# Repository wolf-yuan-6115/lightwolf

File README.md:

# LightWolf

> Sponsored by [Hack Club Blueprint](https://blueprint.hackclub.com/r/137?ref=r) program
> 
> To meet program requirements, `JOURNAL.md` and `bom.csv` files are included in this repository root.

LightWolf is a recreate version of Raspberry Pi Pico development board created by me. It's used to experiment with PCB designing and electronics.

Currently, LightWolf comes with following vairants:
- **LightWolf 2350** (`/2350`): Raspberry Pi RP2350 based development board with 4 MB of flash, USB C connector, a bunch of GPIO pins and 3 user LEDs.

> Depending on my free time, I may create more variants of LightWolf in the future.

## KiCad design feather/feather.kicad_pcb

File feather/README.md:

# Feather

A USB DAC that provides even better audio quality compared to Pumper. Since I want to make the board as small as possible, the board itself is only 6x4 cm.

This board has two outputs: One is 3.5mm unbalanced output, another one is 4.4mm balanced, for headphone that supports this and it can provide more power through this port.

## Why Feather?

Due to being *half* Hi-Fi fan, I want to try out some new method to get better audio. Like previous project Pumper, already got amazing power to drive headphone. Though it has some flaw and I think it's got not very balanced sound profile.

Feather is aimed to elimate the problem encountered on Pumper, with improved DAC and op-amp and one more balanced output. It should be a lot better at driving headphone and provide good audio.

## Images

> It's a 4 layer board, with dedicated GND plane and power plane.

## BOM

| Name         | Cost        |
| ------------ | ----------- |
| PCB Shipping | $4.86       |
| PCB Assambly | $117.63     |
| PCB          | $7.00       |
| Coupon       | $-9.00      |
| **Total**    | **$120.49** |

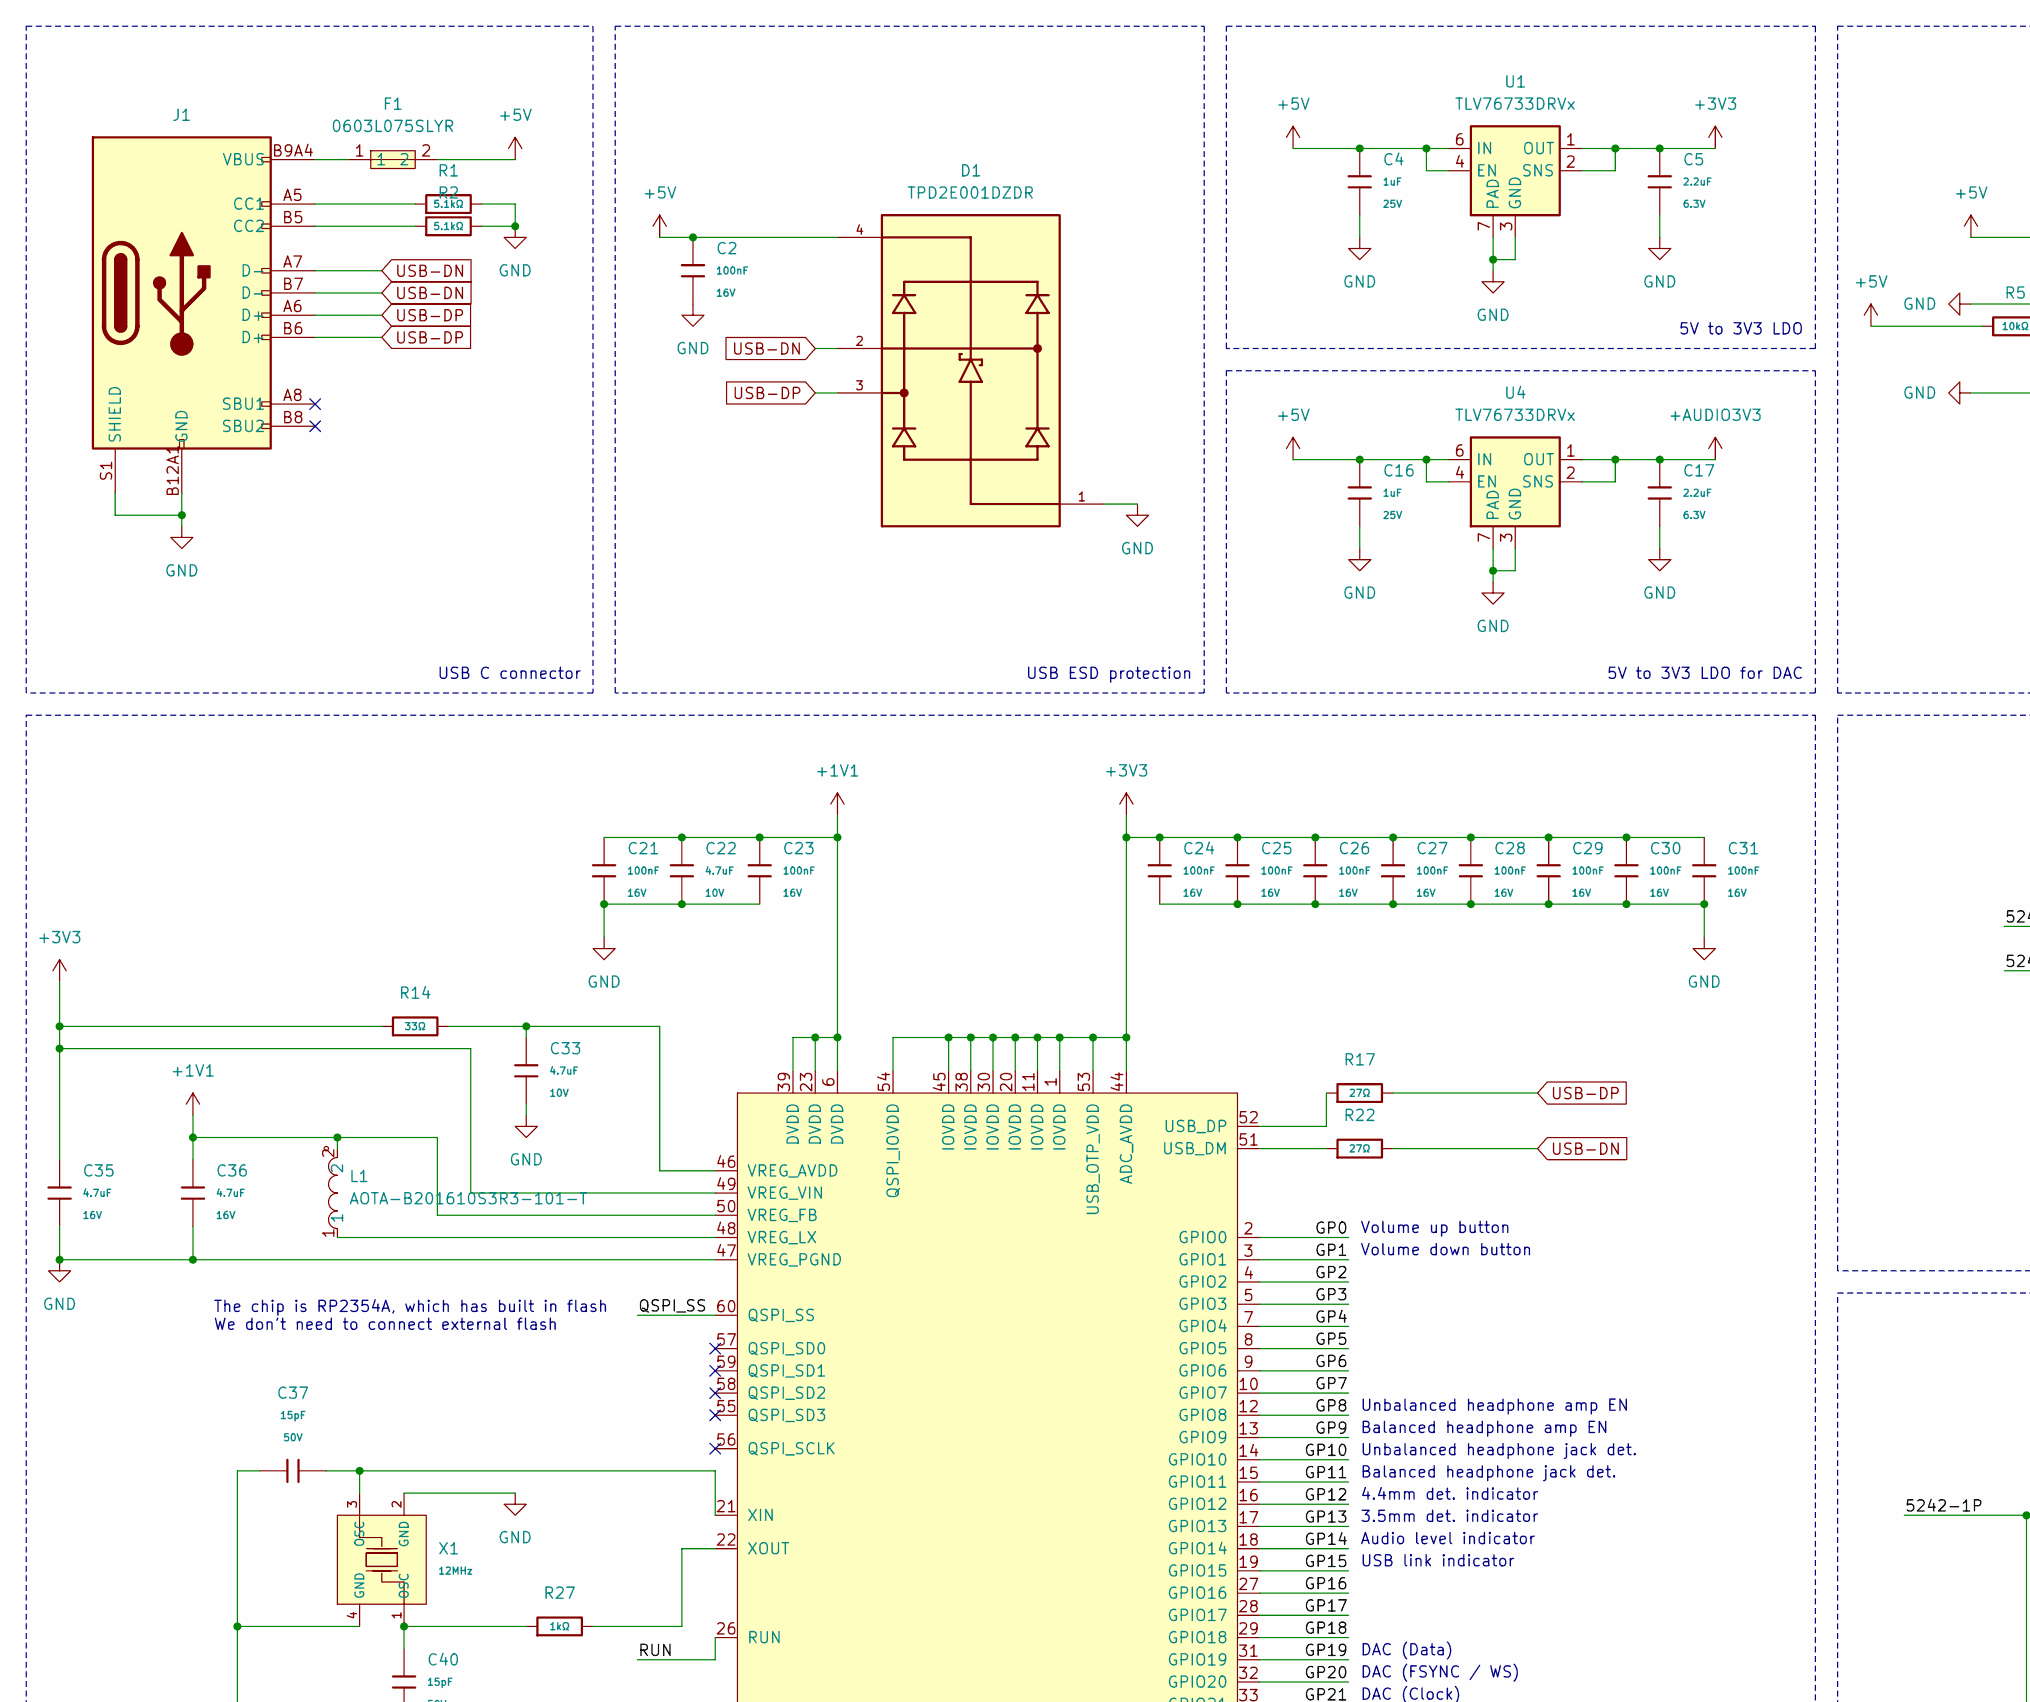
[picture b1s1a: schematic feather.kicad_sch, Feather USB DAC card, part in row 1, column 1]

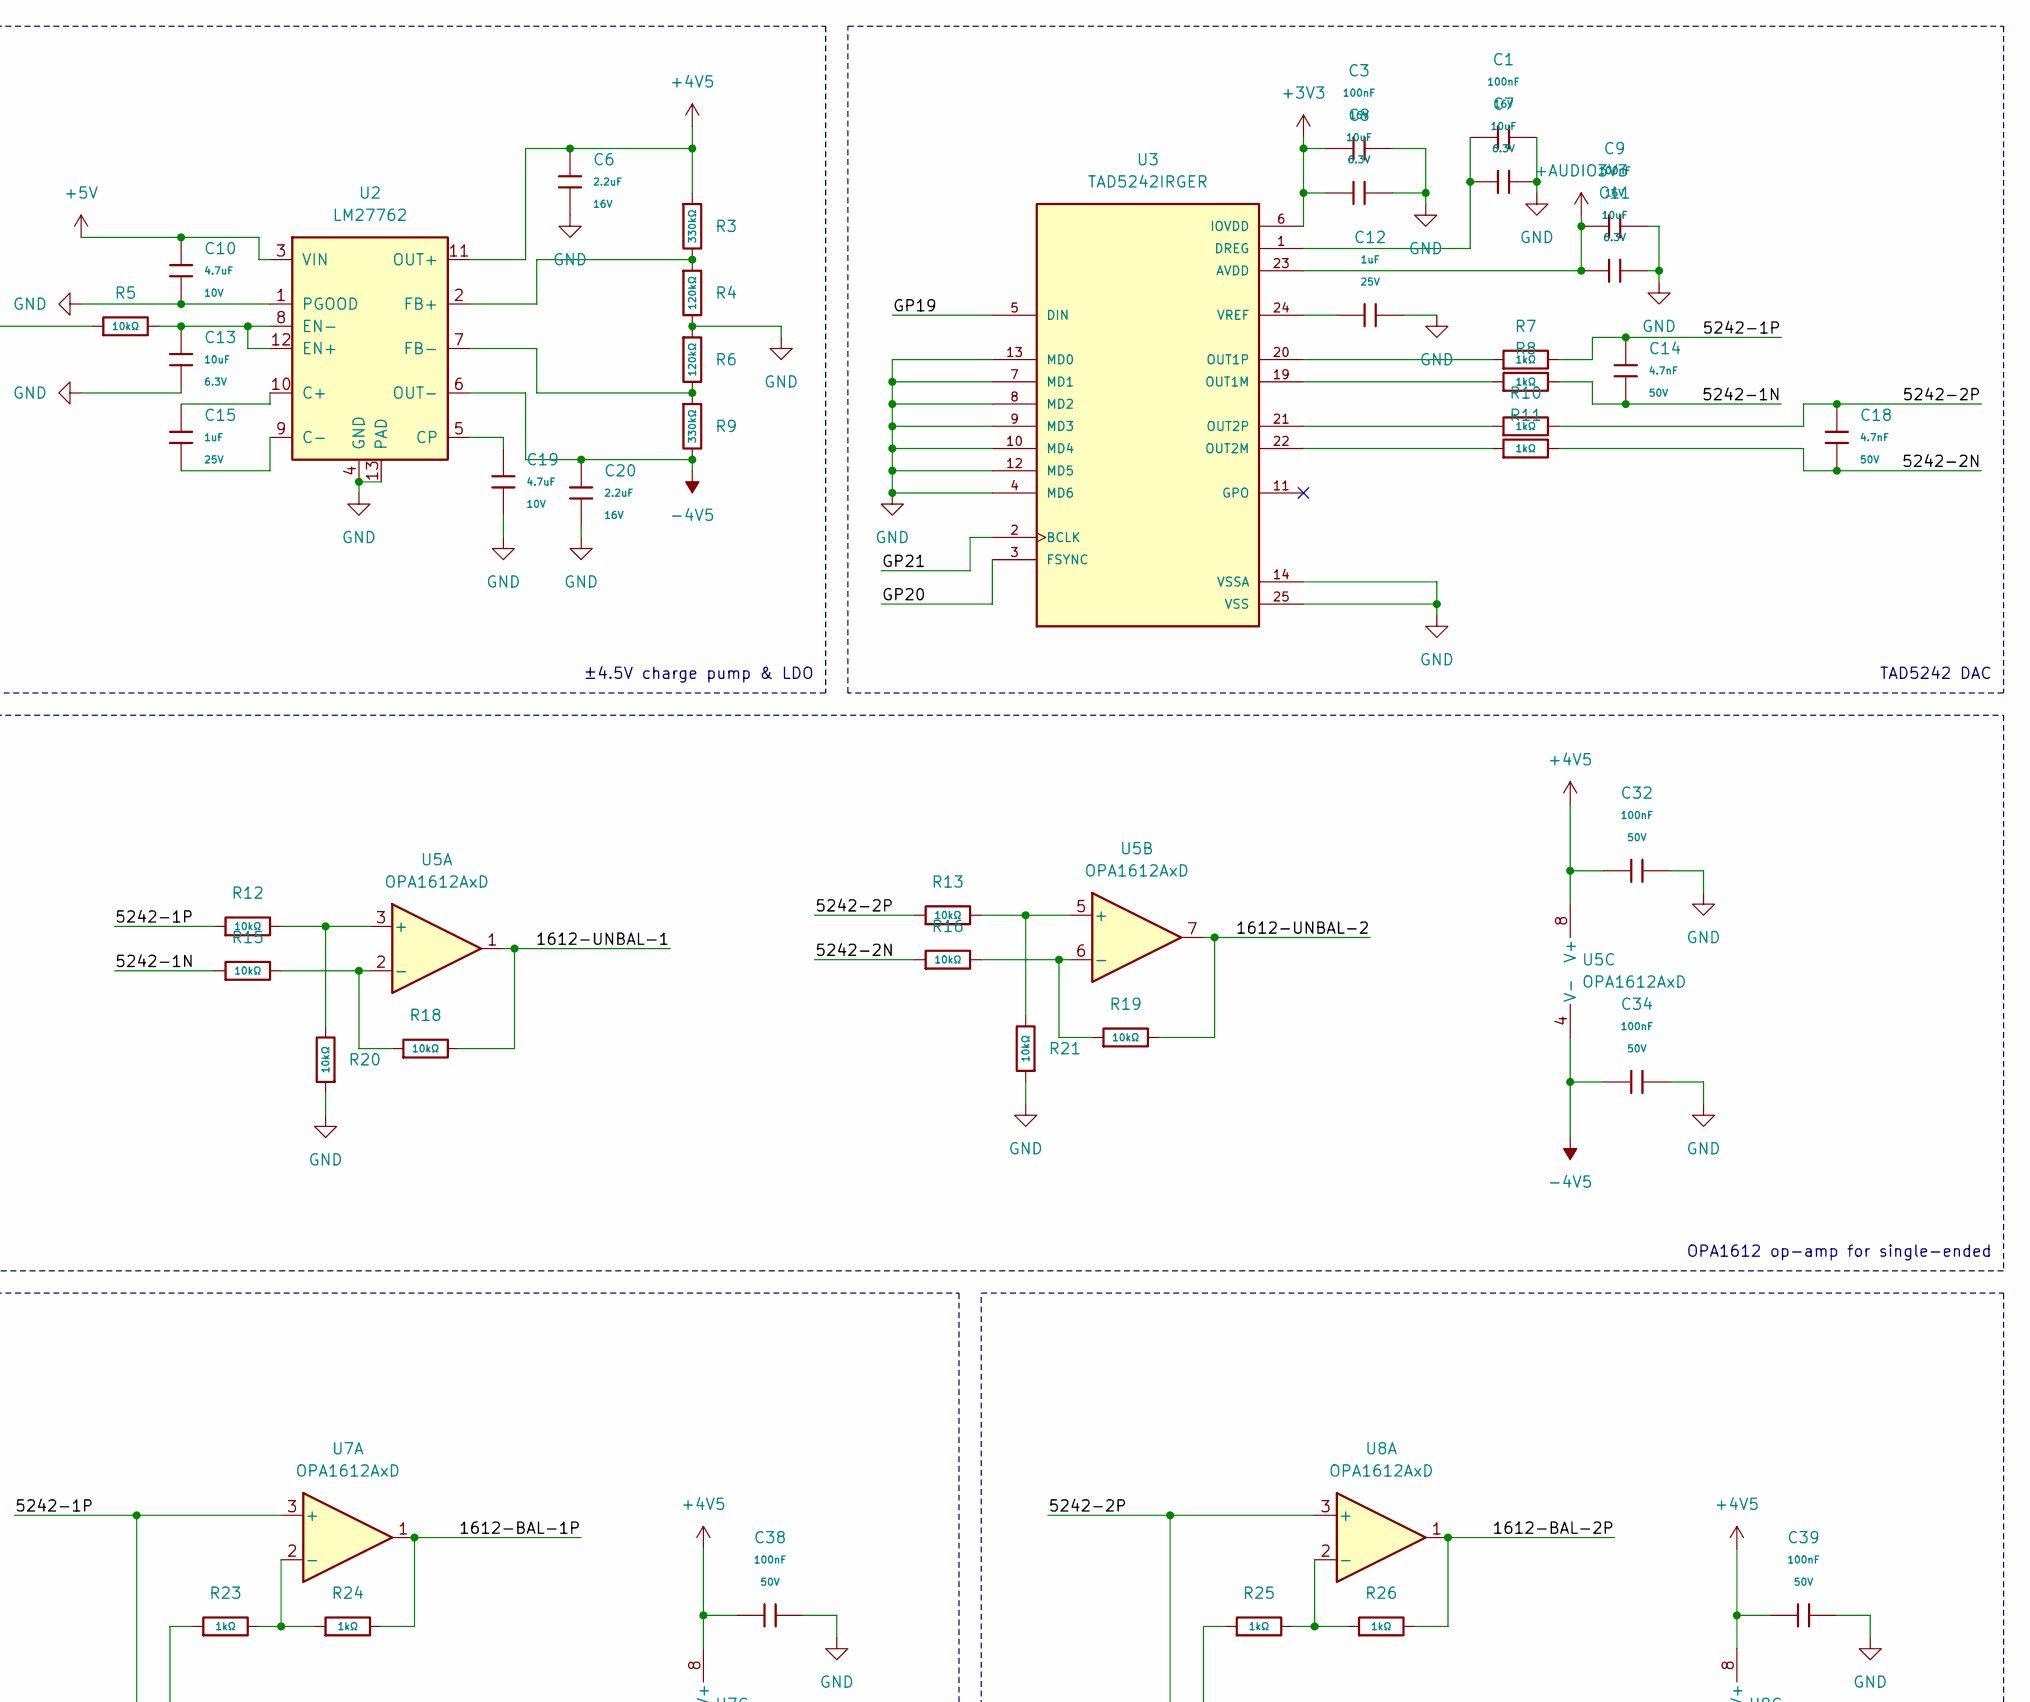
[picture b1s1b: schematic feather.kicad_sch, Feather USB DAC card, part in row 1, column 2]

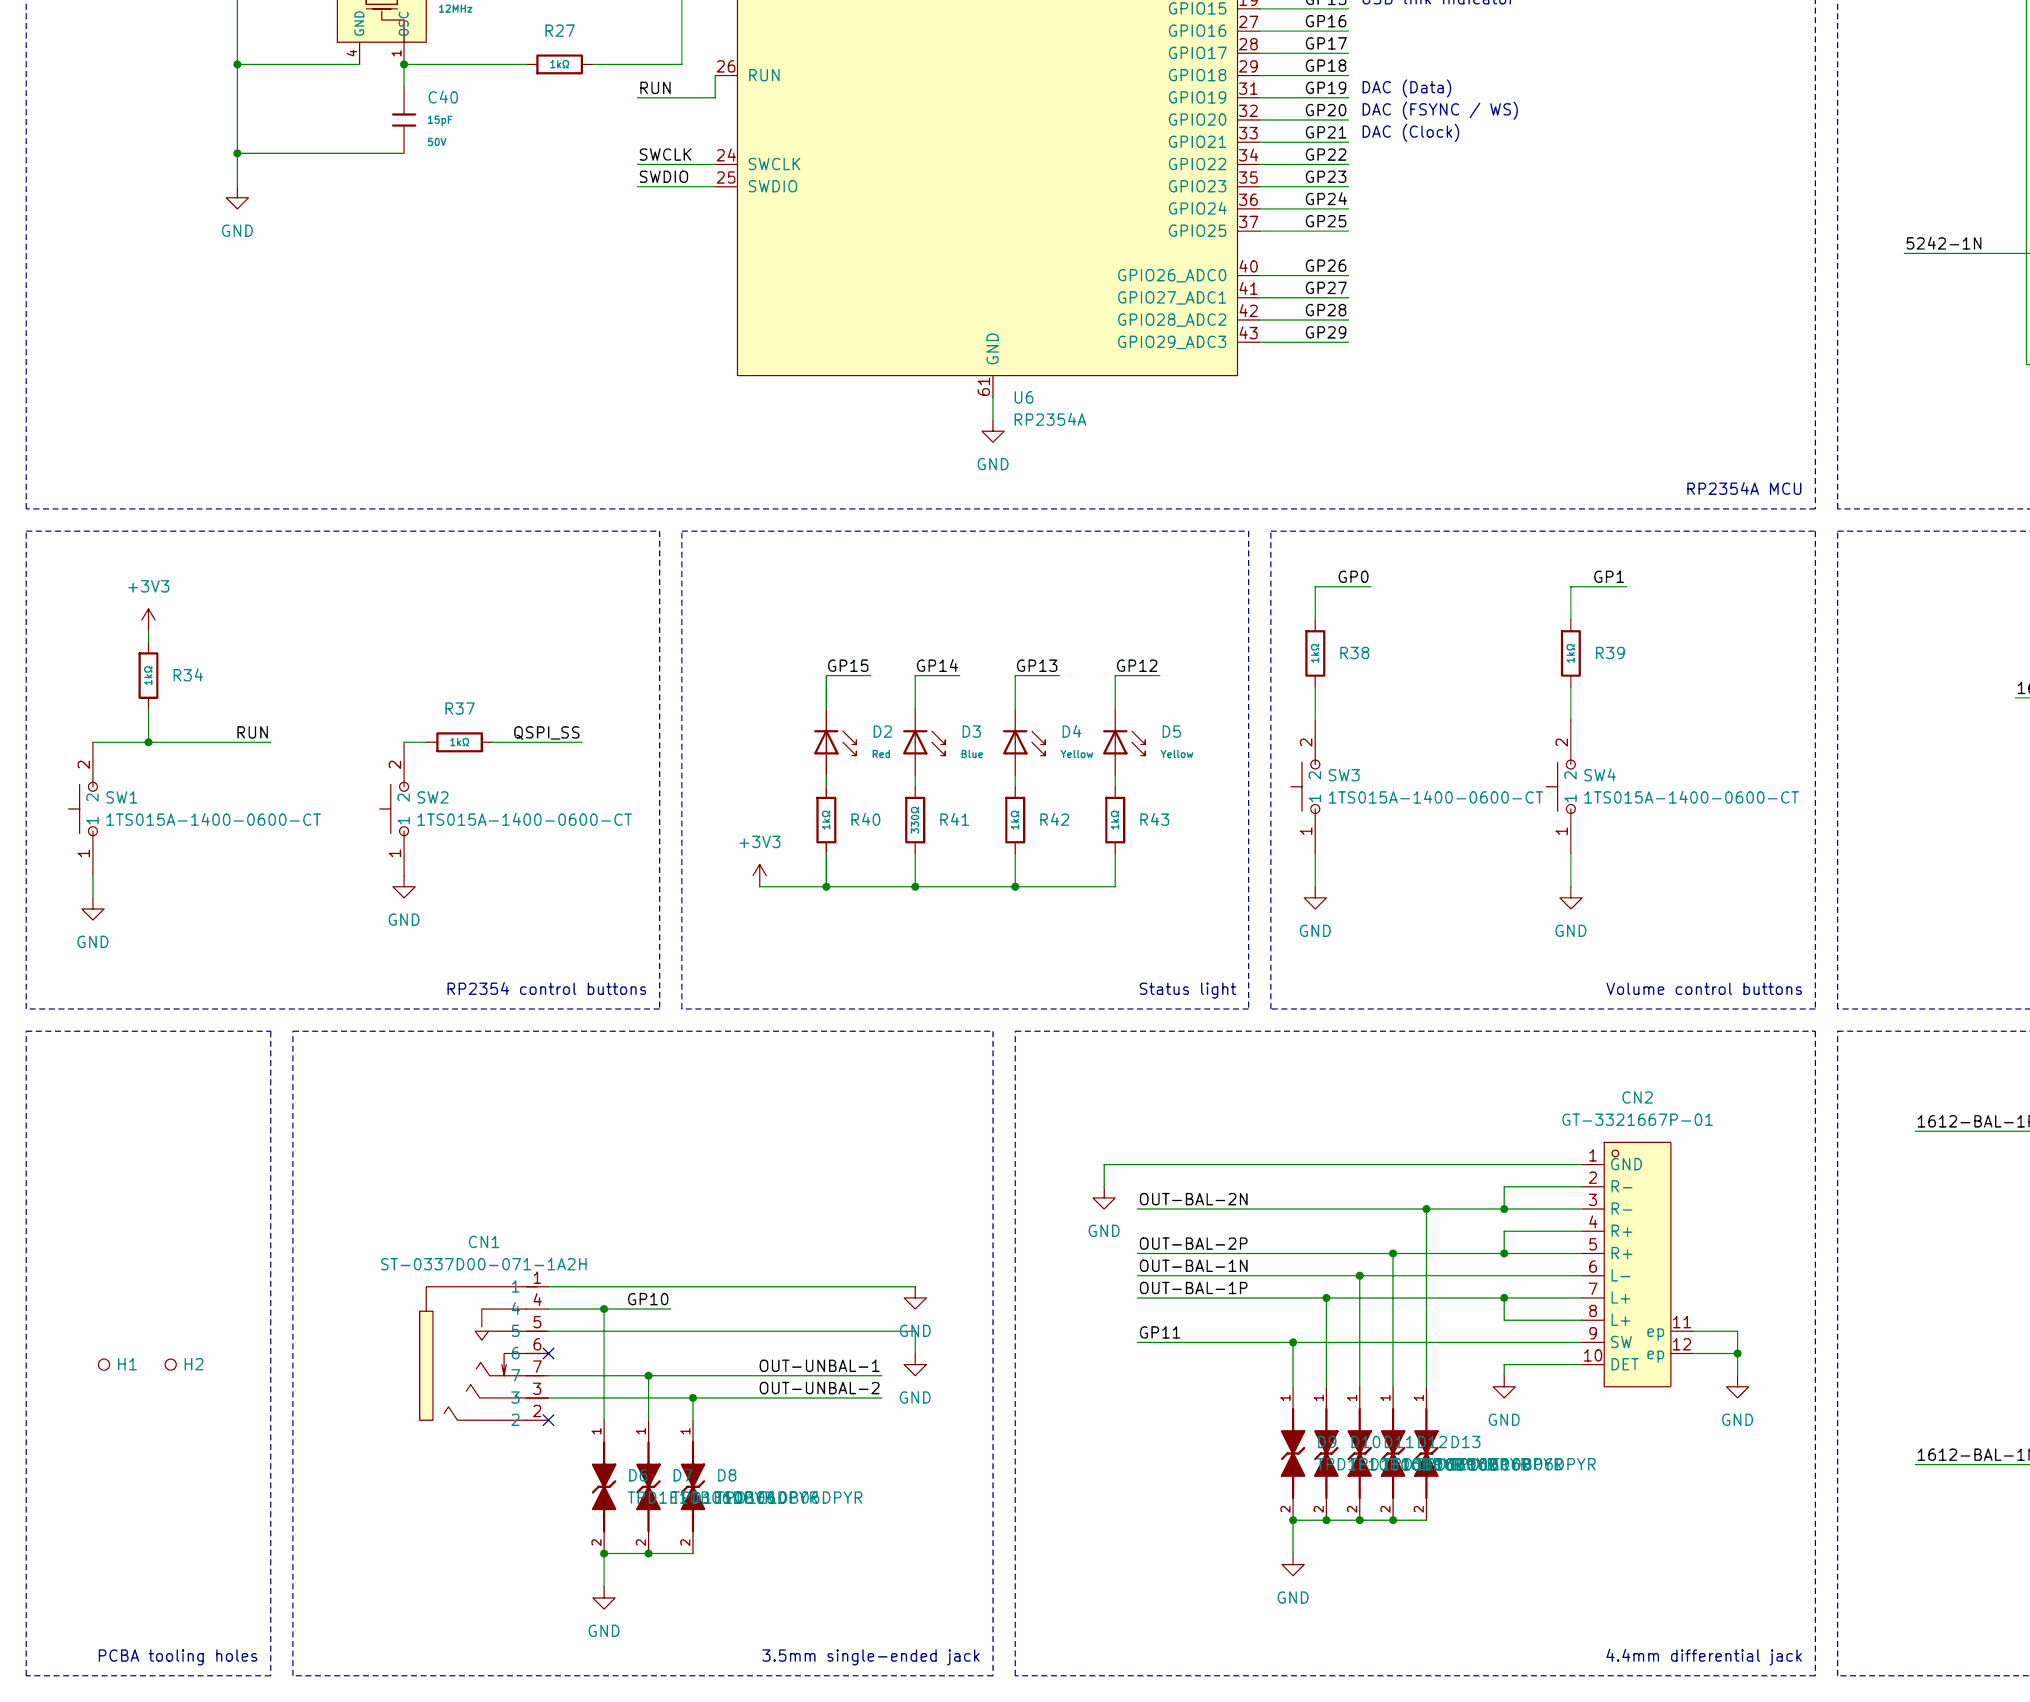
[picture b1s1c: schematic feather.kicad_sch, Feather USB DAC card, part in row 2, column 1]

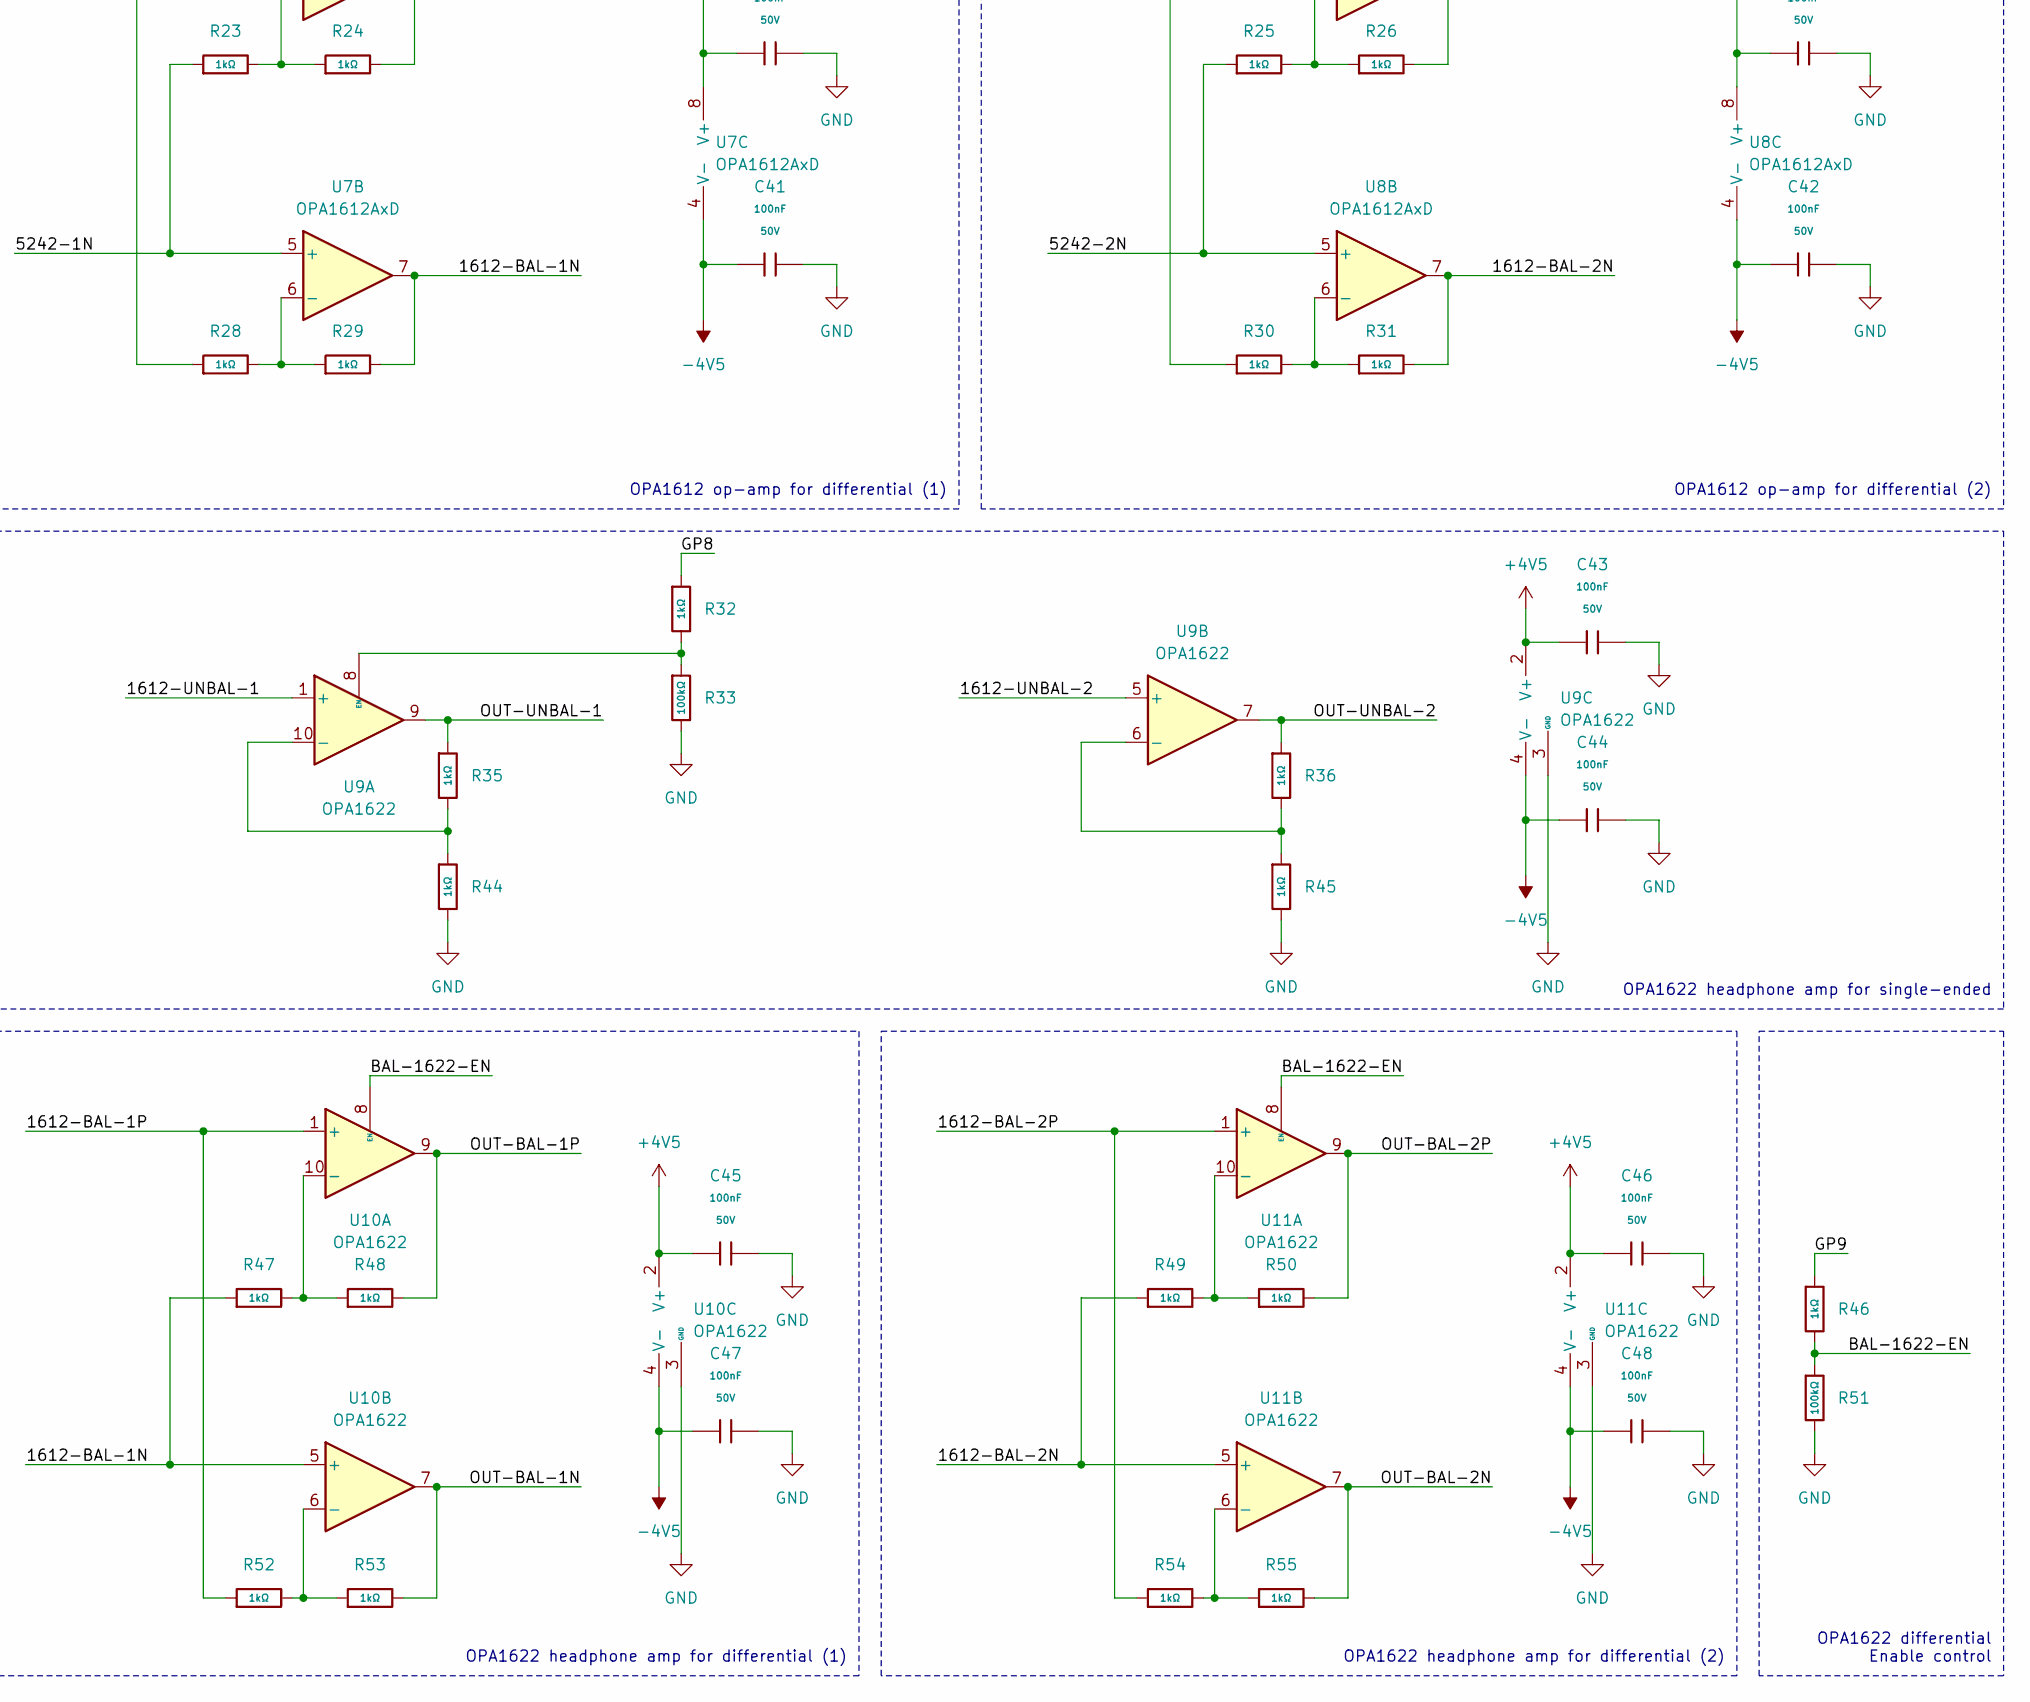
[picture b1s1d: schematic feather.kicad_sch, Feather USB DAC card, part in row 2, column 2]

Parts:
C1, C2, C3, C9, C21, C23, C24, C25, C26, C27, C28, C29, C30, C31: 100nF; C_0402; Voltage Rated 16V; Tolerance ±10%; Part CL05B104KO5NNNC; LCSC C1525
C4, C12, C15, C16: 1uF; C_0402; Voltage Rated 25V; Tolerance ±10%; Part CL05A105KA5NQNC; LCSC C52923
C5, C17: 2.2uF; C_0402; Voltage Rated 6.3V; Tolerance ±20%; Part CL05A225MQ5NSNC; LCSC C12530
C6, C20: 2.2uF; C_0603; Voltage Rated 16V; Tolerance ±10%; Part CL10A225KO8NNNC; LCSC C23630
C7, C8, C11, C13: 10uF; C_0402; Voltage Rated 6.3V; Tolerance ±20%; Part CL05A106MQ5NUNC; LCSC C15525
C10, C19, C22, C33: 4.7uF; C_0402; Voltage Rated 10V; Tolerance ±20%; Part CL05A475MP5NRNC; LCSC C23733
C14, C18: 4.7nF; C_0402; Voltage Rated 50V; Tolerance ±10%; Part 0402B472K500NT; LCSC C1538
C32: 100nF; C_0402; Voltage Rated 50V; Tolerance ±10%; Part CL05B104KB54PNC; LCSC C1525
C34, C38, C39, C41, C42, C43, C44, C45, C46, C47, C48: 100nF; C_0402; Voltage Rated 50V; Tolerance ±10%; Part CL05B104KB54PNC; LCSC C307331
C35, C36: 4.7uF; C_0603; Voltage Rated 16V; Tolerance ±10%; Part CL10A475KO8NNNC; LCSC C19666
C37, C40: 15pF; C_0402; Voltage Rated 50V; Tolerance ±5%; Part 0402CG150J500NT; LCSC C1548
CN1: ST-0337D00-071-1A2H; AUDIO-TH_ST-0337D00-071-1A2H; MPN ST-0337D00-071-1A2H; LCSC Part C2829972
CN2: GT-3321667P-01; AUDIO-TH_GT-3321667P-01; MPN GT-3321667P-01; LCSC Part C2762984
D1: TPD2E001DZDR; SOT192P237X122-4N; PARTREV I; LCSC C89411
D2: Red; D_0603; Forward Voltage (VF) 1.6V~2.6V; Part KT-0603R; LCSC C2286
D3: Blue; D_0603; LCSC C7496823
D4, D5: Yellow; D_0603; Forward Voltage (VF) 1.6V~2.6V; Part NCD0603Y2; LCSC C89811
D6, D7, D8, D9, D10, D11, D12, D13: TPD1E10B06DPYR; DIO_TPD1E10B06DPYR; PARTREV G; LCSC C48260
F1: 0603L075SLYR; Fuse_0603_1608Metric; LCSC Part C207016
H1, H2: Hole_Tooling_JLCPCB
J1: Connector, USB-TYPE-C-16P; TYPE-C-SMD_HX-TYPE-C-16PIN; LCSC C2927039
L1: AOTA-B201610S3R3-101-T; IND-SMD_L2.0-W1.6_AOTA-B201610S3R3-101-T; LCSC Part C42411119
R1, R2: 5.1kΩ; R_0402; Overload Voltage (Max) 50V; Tolerance ±1%; Part 0402WGF5101TCE; LCSC C25905
R3, R9: 330kΩ; R_0603; Overload Voltage (Max) 75V; Tolerance ±1%; Part 0603WAF3303T5E; LCSC C23137
R4, R6: 120kΩ; R_0603; Overload Voltage (Max) 75V; Tolerance ±1%; Part 0603WAF1203T5E; LCSC C25808
R5, R18, R19, R20, R21: 10kΩ; R_0402; Overload Voltage (Max) 50V; Tolerance ±1%; Part 0402WGF1002TCE; LCSC C25744
R7, R8, R10, R11, R23, R24, R25, R26, R27, R28, R29, R30, R31, R32, R34, R35, R36, R37, R38, R39, R40, R42, R43, R44, R45, R46, R47, R48, R49, R50, R52, R53, R54, R55: 1kΩ; R_0402; Overload Voltage (Max) 50V; Tolerance ±1%; Part 0402WGF1001TCE; LCSC C11702
R12, R13, R15, R16: 10kΩ; R_0603; Overload Voltage (Max) 75V; Tolerance ±1%; Part 0603WAF1002T5E; LCSC C25804
R14: 33Ω; R_0402; Overload Voltage (Max) 50V; Tolerance ±1%; Part 0402WGF330JTCE; LCSC C25105
R17, R22: 27Ω; R_0603; Overload Voltage (Max) 75V; Tolerance ±1%; Part 0603WAF270JT5E; LCSC C25190
R33, R51: 100kΩ; R_0402; Overload Voltage (Max) 50V; Tolerance ±1%; Part 0402WGF1003TCE; LCSC C25741
R41: 330Ω; R_0402; Overload Voltage (Max) 50V; Tolerance ±1%; Part 0402WGF3300TCE; LCSC C25104
SW1, SW2, SW3, SW4: 1TS015A-1400-0600-CT; SW-SMD_L3.0-W2.0-LS3.5; LCSC Part C319433
U1, U4: TLV76733DRVx; WSON-6-1EP_2x2mm_P0.65mm_EP1x1.6mm_ThermalVias; LCSC C2848334
U2: LM27762; WSON-12-1EP_3x2mm_P0.5mm_EP1x2.65_ThermalVias; LCSC C473398
U3: TAD5242IRGER; IC_TAD5242IRGER; PARTREV A; LCSC C42414591
U5, U7, U8: OPA1612AxD; WSON-8-1EP_3x3mm_P0.5mm_EP1.2x2mm_ThermalVias; LCSC C2058640
U6: RP2354A; QFN-60-1EP_7x7mm_P0.4mm_EP3.4x3.4mm_ThermalVias; LCSC C42411118
U9, U10, U11: OPA1622; Texas_S-PVSON-N10_ThermalVias; LCSC C2876559
X1: 12MHz; OSC-SMD_4P-L3.2-W2.5-BL_SIT8008BI; LCSC C20625731

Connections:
+1V1: C21.1, C22.1, C23.1, C36.1, L1.2, U6.6 (DVDD), U6.23 (DVDD), U6.39 (DVDD), U6.50 (VREG_FB)
+3V3: C3.1, C5.1, C8.1, C24.1, C25.1, C26.1, C27.1, C28.1, C29.1, C30.1, C31.1, C35.1, R14.1, R34.1, R40.2, R41.2, R42.2, R43.2, U1.1 (OUT), U1.2 (SNS), U3.6 (IOVDD), U6.1 (IOVDD), U6.11 (IOVDD), U6.20 (IOVDD), U6.30 (IOVDD), U6.38 (IOVDD), U6.44 (ADC_AVDD), U6.45 (IOVDD), U6.49 (VREG_VIN), U6.53 (USB_OTP_VDD), U6.54 (QSPI_IOVDD)
+4V5: C6.1, C32.1, C38.1, C39.1, C43.1, C45.1, C46.1, R3.1, U2.11 (OUT+), U5.8 (V+), U7.8 (V+), U8.8 (V+), U9.2 (V+), U10.2 (V+), U11.2 (V+)
+5V: C2.1, C4.1, C10.1, C16.1, D1.4, F1.2, R5.1, U1.4 (EN), U1.6 (IN), U2.3 (VIN), U4.4 (EN), U4.6 (IN)
+AUDIO3V3: C9.1, C11.1, C17.1, U3.23 (AVDD), U4.1 (OUT), U4.2 (SNS)
-4V5: C20.1, C34.1, C41.1, C42.1, C44.1, C47.1, C48.1, R9.2, U2.6 (OUT-), U5.4 (V-), U7.4 (V-), U8.4 (V-), U9.4 (V-), U9.11 (V-), U10.4 (V-), U10.11 (V-), U11.4 (V-), U11.11 (V-)
/1612-BAL-1N: R29.2, R47.1, U7.7, U10.5 (+)
/1612-BAL-1P: R24.2, R52.1, U7.1, U10.1 (+)
/1612-BAL-2N: R31.2, R49.1, U8.7, U11.5 (+)
/1612-BAL-2P: R26.2, R54.1, U8.1, U11.1 (+)
/1612-UNBAL-1: R18.2, U5.1, U9.1 (+)
/1612-UNBAL-2: R19.2, U5.7, U9.5 (+)
/5242-1N: C14.2, R8.2, R15.1, R23.1, U7.5 (+)
/5242-1P: C14.1, R7.2, R12.1, R28.1, U7.3 (+)
/5242-2N: C18.2, R11.2, R16.1, R25.1, U8.5 (+)
/5242-2P: C18.1, R10.2, R13.1, R30.1, U8.3 (+)
/BAL-1622-EN: R46.2, R51.1, U10.8 (EN), U11.8 (EN)
/GP0: R38.1, U6.2 (GPIO0)
/GP1: R39.1, U6.3 (GPIO1)
/GP2: U6.4 (GPIO2)
/GP3: U6.5 (GPIO3)
/GP4: U6.7 (GPIO4)
/GP5: U6.8 (GPIO5)
/GP6: U6.9 (GPIO6)
/GP7: U6.10 (GPIO7)
/GP8: R32.1, U6.12 (GPIO8)
/GP9: R46.1, U6.13 (GPIO9)
/GP10: CN1.4, D6.1, U6.14 (GPIO10)
/GP11: CN2.9 (SW), D9.1, U6.15 (GPIO11)
/GP12: D5.1, U6.16 (GPIO12)
/GP13: D4.1, U6.17 (GPIO13)
/GP14: D3.1, U6.18 (GPIO14)
/GP15: D2.1, U6.19 (GPIO15)
/GP16: U6.27 (GPIO16)
/GP17: U6.28 (GPIO17)
/GP18: U6.29 (GPIO18)
/GP19: U3.5 (DIN), U6.31 (GPIO19)
/GP20: U3.3 (FSYNC), U6.32 (GPIO20)
/GP21: U3.2 (BCLK), U6.33 (GPIO21)
/GP22: U6.34 (GPIO22)
/GP23: U6.35 (GPIO23)
/GP24: U6.36 (GPIO24)
/GP25: U6.37 (GPIO25)
/GP26: U6.40 (GPIO26_ADC0)
/GP27: U6.41 (GPIO27_ADC1)
/GP28: U6.42 (GPIO28_ADC2)
/GP29: U6.43 (GPIO29_ADC3)
/OUT-BAL-1N: CN2.6 (L-), D11.1, R53.2, U10.7
/OUT-BAL-1P: CN2.7 (L+), CN2.8 (L+), D10.1, R48.2, U10.9
/OUT-BAL-2N: CN2.2 (R-), CN2.3 (R-), D13.1, R55.2, U11.7
/OUT-BAL-2P: CN2.4 (R+), CN2.5 (R+), D12.1, R50.2, U11.9
/OUT-UNBAL-1: CN1.7, D7.1, R35.1, U9.9
/OUT-UNBAL-2: CN1.3, D8.1, R36.1, U9.7
/QSPI_SS: R37.2, U6.60 (QSPI_SS)
/RUN: R34.2, SW1.2, U6.26 (RUN)
/SWCLK: U6.24 (SWCLK)
/SWDIO: U6.25 (SWDIO)
GND: C1.2, C2.2, C3.2, C4.2, C5.2, C6.2, C7.2, C8.2, C9.2, C10.2, C11.2, C12.2, C13.2, C16.2, C17.2, C19.2, C20.2, C21.2, C22.2, C23.2, C24.2, C25.2, C26.2, C27.2, C28.2, C29.2, C30.2, C31.2, C32.2, C33.2, C34.2, C35.2, C36.2, C37.1, C38.2, C39.2, C40.2, C41.2, C42.2, C43.2, C44.2, C45.2, C46.2, C47.2, C48.2, CN1.1, CN1.5, CN2.1 (GND), CN2.10 (DET), CN2.11 (ep), CN2.12 (ep), D1.1, D6.2, D7.2, D8.2, D9.2, D10.2, D11.2, D12.2, D13.2, J1.A12B1 (GND), J1.B12A1 (GND), J1.S1 (SHIELD), R1.2, R2.2, R4.2, R6.1, R20.1, R21.1, R33.2, R44.2, R45.2, R51.2, SW1.1, SW2.1, SW3.1, SW4.1, U1.3 (GND), U1.5 (GND), U1.7 (PAD), U2.1 (PGOOD), U2.4 (GND), U2.13 (PAD), U3.4 (MD6), U3.7 (MD1), U3.8 (MD2), U3.9 (MD3), U3.10 (MD4), U3.12 (MD5), U3.13 (MD0), U3.14 (VSSA), U3.15 (VSSA), U3.16 (VSSA), U3.17 (VSSA), U3.18 (VSSA), U3.25 (VSS), U3.A1 (VSS), U3.A2 (VSS), U3.A3 (VSS), U3.A4 (VSS), U4.3 (GND), U4.5 (GND), U4.7 (PAD), U6.47 (VREG_PGND), U6.61 (GND), U9.3 (GND), U10.3 (GND), U11.3 (GND), X1.2 (GND), X1.4 (GND)
unnamed: C40.1, R27.1, X1.1 (OSC)
unnamed: D2.2, R40.1
unnamed: D3.2, R41.1
unnamed: D4.2, R42.1
unnamed: D5.2, R43.1
unnamed: F1.1, J1.A9B4 (VBUS), J1.B9A4 (VBUS)
unnamed: J1.A5 (CC1), R1.1
unnamed: J1.B5 (CC2), R2.1
unnamed: R37.1, SW2.2
unnamed: R38.2, SW3.2
unnamed: R39.2, SW4.2
unnamed: C15.1, U2.10 (C+)
unnamed: C15.2, U2.9 (C-)
unnamed: C19.1, U2.5 (CP)
unnamed: C13.1, R5.2, U2.8 (EN-), U2.12 (EN+)
unnamed: R3.2, R4.1, U2.2 (FB+)
unnamed: R6.2, R9.1, U2.7 (FB-)
unnamed: C1.1, C7.1, U3.1 (DREG)
unnamed: R8.1, U3.19 (OUT1M)
unnamed: R7.1, U3.20 (OUT1P)
unnamed: R11.1, U3.22 (OUT2M)
unnamed: R10.1, U3.21 (OUT2P)
unnamed: C12.1, U3.24 (VREF)
unnamed: R12.2, R20.2, U5.3 (+)
unnamed: R15.2, R18.1, U5.2 (-)
unnamed: R13.2, R21.2, U5.5 (+)
unnamed: R16.2, R19.1, U5.6 (-)
unnamed: R22.1, U6.51 (USB_DM)
unnamed: R17.1, U6.52 (USB_DP)
unnamed: C33.1, R14.2, U6.46 (VREG_AVDD)
unnamed: L1.1, U6.48 (VREG_LX)
unnamed: C37.2, U6.21 (XIN), X1.3 (OSC)
unnamed: R27.2, U6.22 (XOUT)
unnamed: R23.2, R24.1, U7.2 (-)
unnamed: R28.2, R29.1, U7.6 (-)
unnamed: R25.2, R26.1, U8.2 (-)
unnamed: R30.2, R31.1, U8.6 (-)
unnamed: R35.2, R44.1, U9.10 (-)
unnamed: R32.2, R33.1, U9.8 (EN)
unnamed: R36.2, R45.1, U9.6 (-)
unnamed: R47.2, R48.1, U10.10 (-)
unnamed: R52.2, R53.1, U10.6 (-)
unnamed: R49.2, R50.1, U11.10 (-)
unnamed: R54.2, R55.1, U11.6 (-)
USB-DN: D1.2, J1.A7 (D-), J1.B7 (D-), R22.2
USB-DP: D1.3, J1.A6 (D+), J1.B6 (D+), R17.2

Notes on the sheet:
Status light
3.5mm single-ended jack
OPA1622 headphone amp for single-ended
Unbalanced headphone amp EN
OPA1622 headphone amp for differential (1)
RP2354 control buttons
USB link indicator
OPA1622 differential Enable control
USB C connector
5V to 3V3 LDO
Volume up button
OPA1612 op-amp for differential (2)
Unbalanced headphone jack det.
RP2354A MCU
Volume control buttons
DAC (FSYNC / WS)
OPA1612 op-amp for differential (1)
TAD5242 DAC
4.4mm differential jack
Audio level indicator
The chip is RP2354A, which has built in flash We don't need to connect external flash
5V to 3V3 LDO for DAC
DAC (Clock)
PCBA tooling holes
USB ESD protection
Volume down button
4.4mm det. indicator
DAC (Data)
OPA1612 op-amp for single-ended
OPA1622 headphone amp for differential (2)
±4.5V charge pump & LDO
Balanced headphone amp EN
3.5mm det. indicator
Balanced headphone jack det.

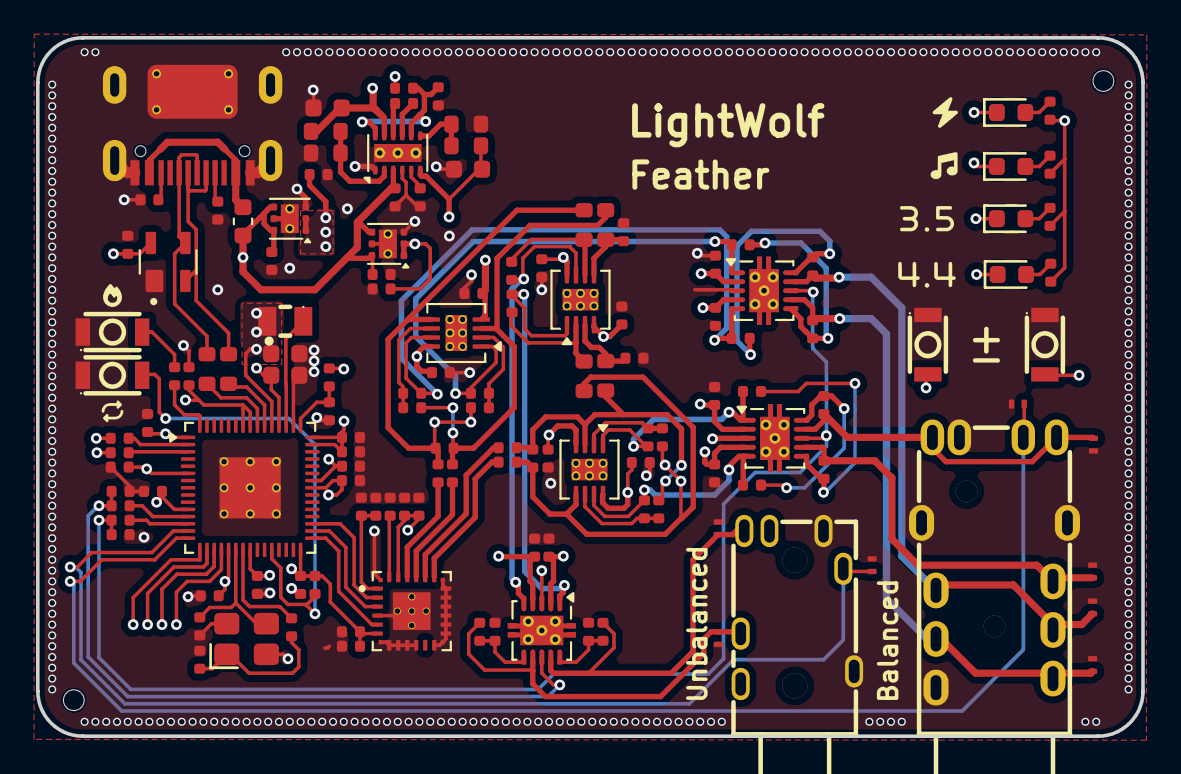
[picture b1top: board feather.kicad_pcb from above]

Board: 4 copper layers, 61.4 x 38.8 mm, 139 parts (0 on the bottom side), 85 nets.

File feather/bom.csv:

Comment,Designator,Footprint,LCSC,Quantity
0603L075SLYR,F1,Fuse_0603_1608Metric,C207016,1
100kΩ,"R33,R51",R_0402,C25741,2
100nF,"C1,C2,C21,C23,C24,C25,C26,C27,C28,C29,C3,C30,C31,C32,C9",C_0402,C1525,15
100nF,"C34,C38,C39,C41,C42,C43,C44,C45,C46,C47,C48",C_0402,C307331,11
10kΩ,"R18,R19,R20,R21,R5",R_0402,C25744,5
10kΩ,"R12,R13,R15,R16",R_0603,C25804,4
10uF,"C11,C13,C7,C8",C_0402,C15525,4
120kΩ,"R4,R6",R_0603,C25808,2
12MHz,X1,OSC-SMD_4P-L3.2-W2.5-BL_SIT8008BI,C20625731,1
15pF,"C37,C40",C_0402,C1548,2
1TS015A-1400-0600-CT,"SW1,SW2,SW3,SW4",SW-SMD_L3.0-W2.0-LS3.5,C319433,4
1kΩ,"R10,R11,R23,R24,R25,R26,R27,R28,R29,R30,R31,R32,R34,R35,R36,R37,R38,R39,R40,R42,R43,R44,R45,R46,R47,R48,R49,R50,R52,R53,R54,R55,R7,R8",R_0402,C11702,34
1uF,"C12,C15,C16,C4",C_0402,C52923,4
2.2uF,"C17,C5",C_0402,C12530,2
2.2uF,"C20,C6",C_0603,C23630,2
27Ω,"R17,R22",R_0603,C25190,2
330kΩ,"R3,R9",R_0603,C23137,2
330Ω,R41,R_0402,C25104,1
33Ω,R14,R_0402,C25105,1
4.7nF,"C14,C18",C_0402,C1538,2
4.7uF,"C35,C36",C_0603,C19666,2
4.7uF,"C10,C19,C22,C33",C_0402,C23733,4
5.1kΩ,"R1,R2",R_0402,C25905,2
AOTA-B201610S3R3-101-T,L1,IND-SMD_L2.0-W1.6_AOTA-B201610S3R3-101-T,C42411119,1
Blue,D3,D_0603,C7496823,1
"Connector, USB-TYPE-C-16P",J1,TYPE-C-SMD_HX-TYPE-C-16PIN,C2927039,1
GT-3321667P-01,CN2,AUDIO-TH_GT-3321667P-01,C2762984,1
LM27762,U2,WSON-12-1EP_3x2mm_P0.5mm_EP1x2.65_ThermalVias,C473398,1
OPA1612AxD,"U5,U7,U8",WSON-8-1EP_3x3mm_P0.5mm_EP1.2x2mm_ThermalVias,C2058640,3
OPA1622,"U10,U11,U9",Texas_S-PVSON-N10_ThermalVias,C2876559,3
RP2354A,U6,QFN-60-1EP_7x7mm_P0.4mm_EP3.4x3.4mm_ThermalVias,C42411118,1
Red,D2,D_0603,C2286,1
ST-0337D00-071-1A2H,CN1,AUDIO-TH_ST-0337D00-071-1A2H,C2829972,1
TAD5242IRGER,U3,IC_TAD5242IRGER,C42414591,1
TLV76733DRVx,"U1,U4",WSON-6-1EP_2x2mm_P0.65mm_EP1x1.6mm_ThermalVias,C2848334,2
TPD1E10B06DPYR,"D10,D11,D12,D13,D6,D7,D8,D9",DIO_TPD1E10B06DPYR,C48260,8
TPD2E001DZDR,D1,SOT192P237X122-4N,C89411,1
Yellow,"D4,D5",D_0603,C89811,2
